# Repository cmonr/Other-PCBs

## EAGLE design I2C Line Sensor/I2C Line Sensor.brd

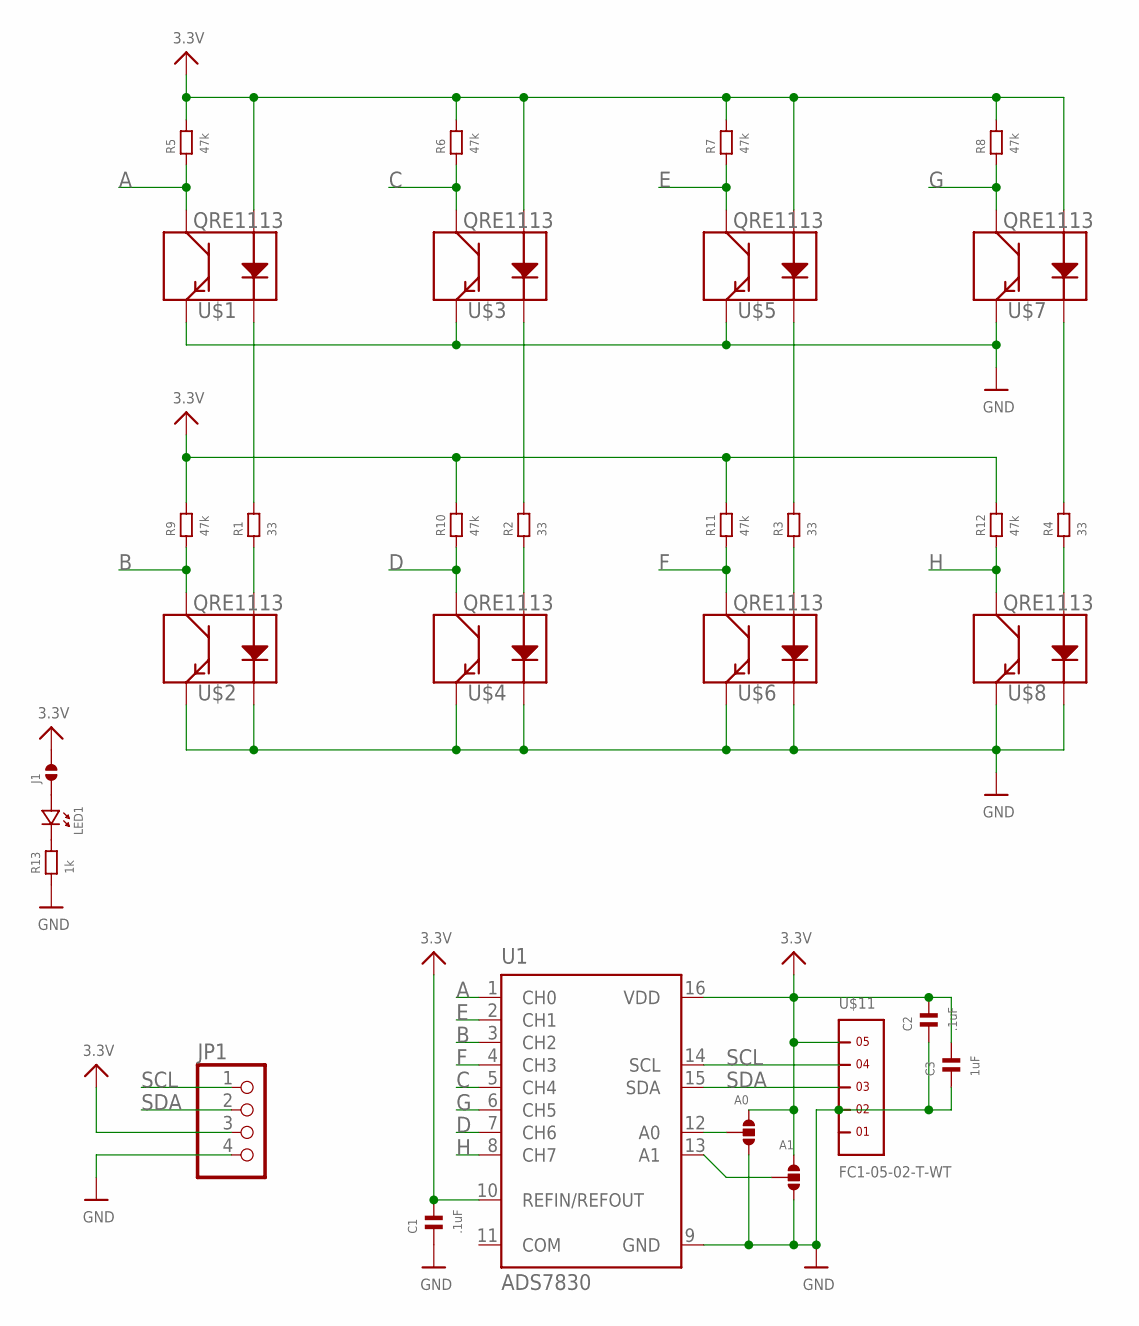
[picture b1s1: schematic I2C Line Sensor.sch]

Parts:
A0, A1: SOLDERJUMPER.3.LRG.23; 3.LRG.23
C1, C2: .1uF; 0603
C3: 1uF; 0603
J1: SOLDERJUMPER.2.MED; 2.MED
JP1: HEADER-1X4; 1X04_OVAL
LED1: LED.0603; 0603.LED
R1, R2, R3, R4: 33; 0603
R5, R6, R7, R8, R9, R10, R11, R12: 47k; 0603
R13: 1k; 0603
U1: ADS7830; TSSOP16-PW
U$1, U$2, U$3, U$4, U$5, U$6, U$7, U$8: QRE1113
U$11: FC1-05-02-T-WT

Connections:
3.3V: A0.1, A1.1, C1.2, C2.2, C3.2, J1.2, JP1.3, R5.2, R6.2, R7.2, R8.2, R9.2, R10.2, R11.2, R12.2, U1.10 (REFIN/REFOUT), U1.16 (VDD), U$1.1 (A), U$3.1 (A), U$5.1 (A), U$7.1 (A), U$11.5
A: R5.1, U1.1 (CH0), U$1.3 (C)
B: R9.1, U1.3 (CH2), U$2.3 (C)
C: R6.1, U1.5 (CH4), U$3.3 (C)
D: R10.1, U1.7 (CH6), U$4.3 (C)
E: R7.1, U1.2 (CH1), U$5.3 (C)
F: R11.1, U1.4 (CH3), U$6.3 (C)
G: R8.1, U1.6 (CH5), U$7.3 (C)
GND: A0.3, A1.3, C1.1, C2.1, C3.1, JP1.4, R13.1, U1.9 (GND), U$1.4 (E), U$2.2 (K), U$2.4 (E), U$3.4 (E), U$4.2 (K), U$4.4 (E), U$5.4 (E), U$6.2 (K), U$6.4 (E), U$7.4 (E), U$8.2 (K), U$8.4 (E), U$11.2
H: R12.1, U1.8 (CH7), U$8.3 (C)
unnamed: A0.2, U1.12 (A0)
unnamed: R1.2, U$1.2 (K)
unnamed: R1.1, U$2.1 (A)
unnamed: R2.1, U$4.1 (A)
unnamed: R2.2, U$3.2 (K)
unnamed: R3.2, U$5.2 (K)
unnamed: R3.1, U$6.1 (A)
unnamed: R4.2, U$7.2 (K)
unnamed: R4.1, U$8.1 (A)
unnamed: A1.2, U1.13 (A1)
unnamed: LED1.P$2 (2), R13.2
unnamed: J1.1, LED1.P$1 (1)
SCL: JP1.1, U1.14 (SCL), U$11.4
SDA: JP1.2, U1.15 (SDA), U$11.3

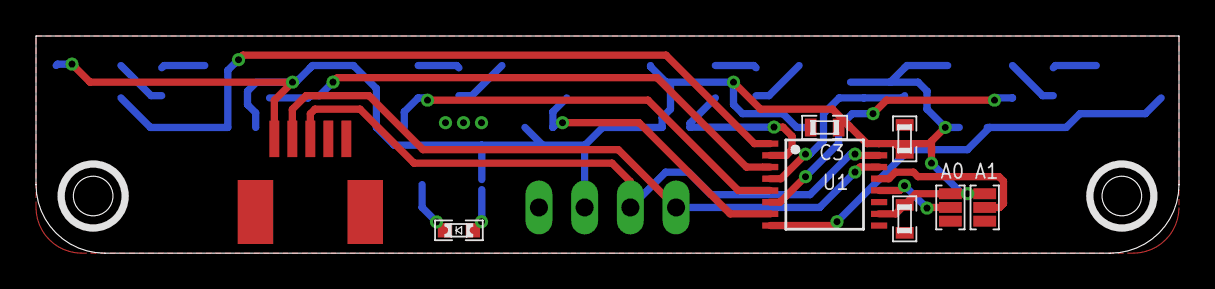
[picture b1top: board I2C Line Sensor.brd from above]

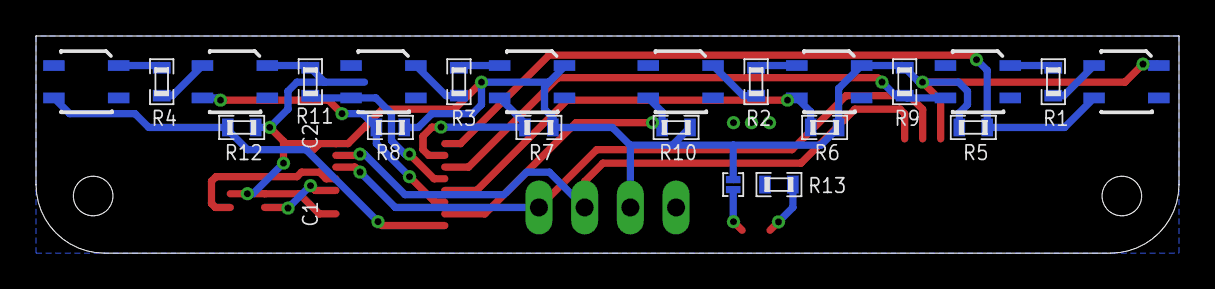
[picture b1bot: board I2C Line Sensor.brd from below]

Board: 2 copper layers, 63.5 x 12.1 mm, 31 parts (22 on the bottom side), 24 nets.

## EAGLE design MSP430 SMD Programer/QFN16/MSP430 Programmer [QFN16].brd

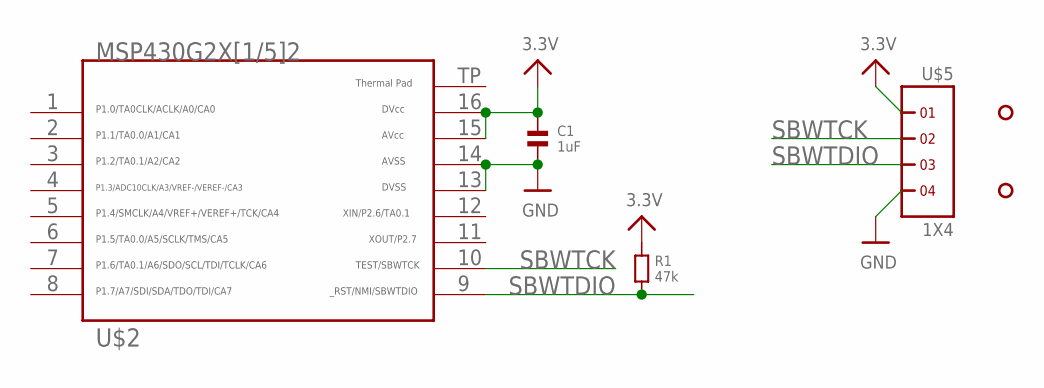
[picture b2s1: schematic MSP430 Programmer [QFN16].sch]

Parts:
C1: 1uF; 0805
R1: 47k; 0805
U$2: G2X[1/5]2---RSA16; RSA16
U$5: 1X4
U$7, U$8: HOLE.2MM; 2MM

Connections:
3.3V: C1.1, R1.1, U$2.15, U$2.16, U$5.1
GND: C1.2, U$2.13, U$2.14, U$5.4
SBWTCK: U$2.10, U$5.2
SBWTDIO: R1.2, U$2.9, U$5.3

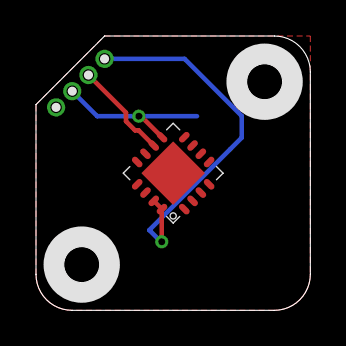
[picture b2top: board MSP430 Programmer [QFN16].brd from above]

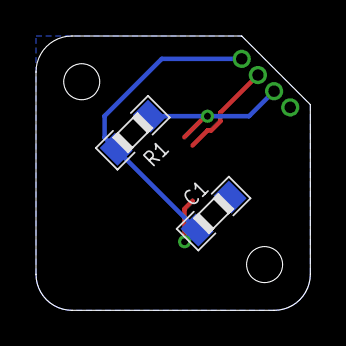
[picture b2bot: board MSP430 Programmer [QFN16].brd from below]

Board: 2 copper layers, 15.2 x 15.2 mm, 6 parts (2 on the bottom side), 4 nets.

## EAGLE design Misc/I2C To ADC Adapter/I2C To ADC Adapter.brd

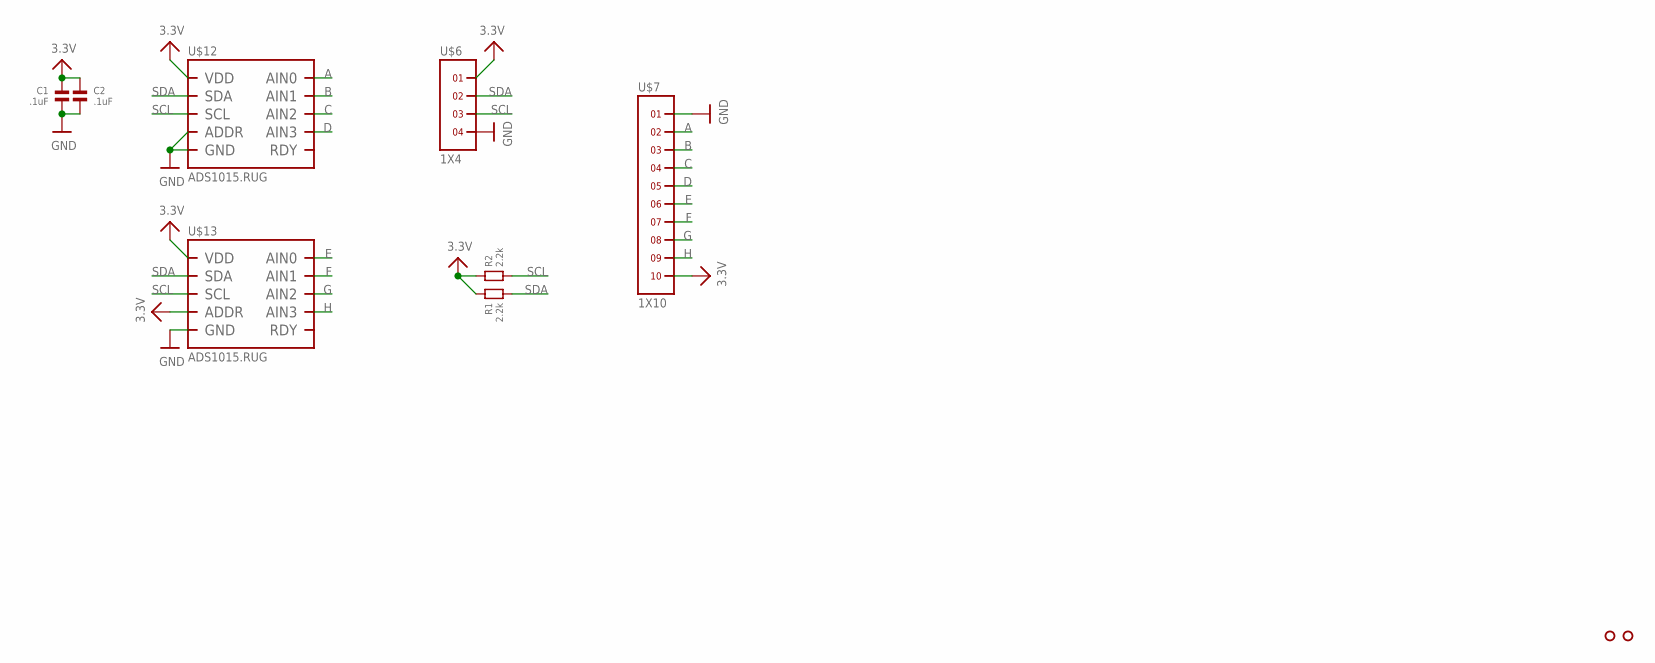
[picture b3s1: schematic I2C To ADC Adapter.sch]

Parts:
C1, C2: .1uF; 0603
R1, R2: 2.2k; 0603
U$3, U$18: HOLE.4MM; 4MM
U$6: 1X4
U$7: 1X10
U$12, U$13: ADS1015.RUG; RUG.10

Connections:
3.3V: C1.1, C2.1, R1.1, R2.1, U$6.1, U$7.10, U$12.8 (VDD), U$13.1 (ADDR), U$13.8 (VDD)
A: U$7.2, U$12.4 (AIN0)
B: U$7.3, U$12.5 (AIN1)
C: U$7.4, U$12.6 (AIN2)
D: U$7.5, U$12.7 (AIN3)
E: U$7.6, U$13.4 (AIN0)
F: U$7.7, U$13.5 (AIN1)
G: U$7.8, U$13.6 (AIN2)
GND: C1.2, C2.2, U$6.4, U$7.1, U$12.1 (ADDR), U$12.3 (GND), U$13.3 (GND)
H: U$7.9, U$13.7 (AIN3)
SCL: R2.2, U$6.3, U$12.10 (SCL), U$13.10 (SCL)
SDA: R1.2, U$6.2, U$12.9 (SDA), U$13.9 (SDA)

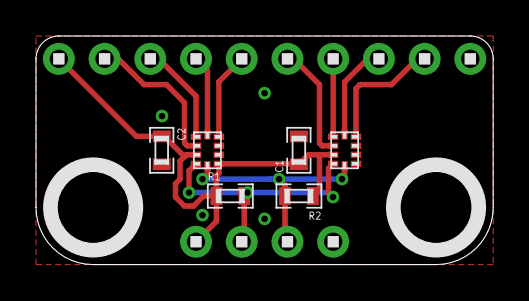
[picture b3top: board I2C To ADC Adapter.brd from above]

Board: 2 copper layers, 25.4 x 12.7 mm, 10 parts (0 on the bottom side), 12 nets.

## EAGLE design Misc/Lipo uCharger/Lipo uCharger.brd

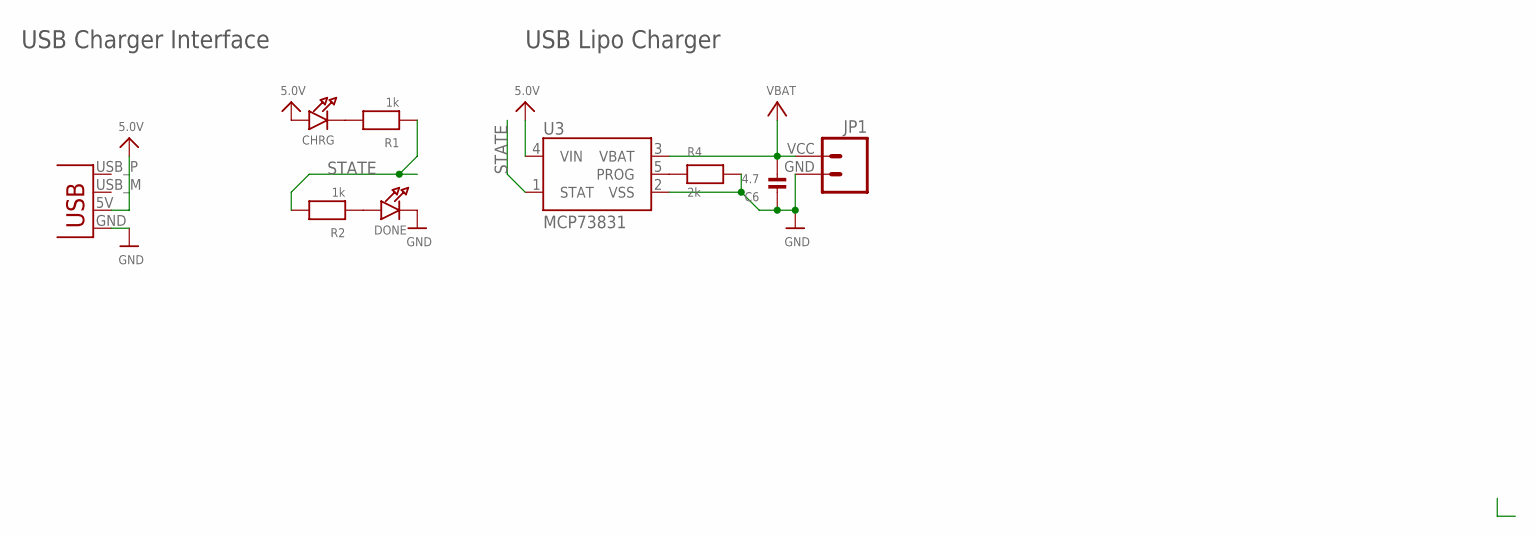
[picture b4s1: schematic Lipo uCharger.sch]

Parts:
C6: 4.7; 0603
CHRG: LED0603; CHIPLED_0603
DONE: LED0603; CHIPLED_0603
JP1: M024UCON-15767; JST-2-SMD-VERT
R1, R2: 1k; 0603
R4: 2k; 0603
U3: MCP73831; SOT23-5
X1: USBPCB; USB-A-PCB

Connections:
5.0V: CHRG.A, U3.4 (VIN), X1.5V (VBUS)
GND: C6.1, DONE.C, JP1.GND (1), R4.2, U3.2 (VSS), X1.GND
unnamed: R4.1, U3.5 (PROG)
unnamed: CHRG.C, R1.2
unnamed: DONE.A, R2.1
STATE: R1.1, R2.2, U3.1 (STAT)
VBAT: C6.2, JP1.VCC (2), U3.3 (VBAT)

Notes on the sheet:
USB Lipo Charger
USB Charger Interface

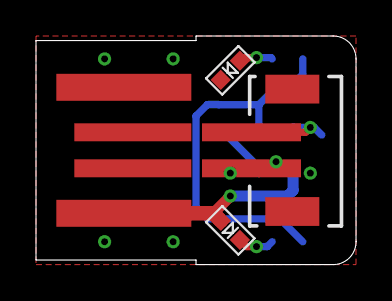
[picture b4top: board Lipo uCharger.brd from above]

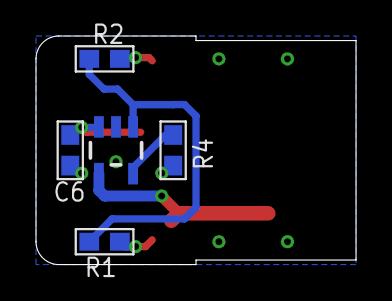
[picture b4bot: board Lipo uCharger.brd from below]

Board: 2 copper layers, 17.8 x 12.7 mm, 9 parts (5 on the bottom side), 7 nets.
